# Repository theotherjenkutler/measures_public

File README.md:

# Measures
## An ecosystem for detection of physiological indicators of empathy.
<p>MEASURES is a flexible web based, AI driven eco-system which lends itself to live performance, 
<br>installation in a gallery museum, festival or alone in one's bedroom while being simple enough 
<br>for anyone with WIFI and a smartphone to use.
<br>It fuses technology and emotion where technology is often sterile and intellectual and offers 
<br>tools for self reflection while creating a method of studying the phenomenon of empathy as a whole. 
<br>Ultimately, MEASURES offers a new way to feel connected and to experience one another across borders, 
<br>cultures, socioeconomic classes and other zones of isolation.

<p>Users wear an electronic wristband which provides audio cues and measures the participant's electrodermal
<br>activity. The data is transferred over WIFI to a server which processes the data and generates a unique sound work.
<br>Each sound work produced by a participant is subsequently analyzed for point of “excitation” using Opensmile 
<br>feature extraction trained by a custom piece specific data set. The results are used as the basis of the following 
<br>user's auditory stimuli and physiological data comparison to generate the next sound piece and so on. The sound 
<br>works are added to a public online archive. Participants can choose to disclose their identity or remain anonymous.
<br>To my knowledge, MEASURES is the first system in the artistic and scientific communities designed with the 
<br>specific purpose of quantifying and measuring empathy from auditory cues. MEASURES content originates from an 
<br>infinitely expansive pool of participant data is comprised of empathetic responses for an AI driven art work.

<p>The goals of this piece put the wealth seeking uses of AI such as advertising, facial/voice recognition, fraud 
<br>prevention and other commercial applications in the background. It focuses on AI as a tool to witness people in 
<br>the most human way possible – through experiencing a person feeling empathy.
<br>The form of MEASURES is also unique because the data collection device exists as an electronic art object and 
<br>generates an expansive bio-data driven archive of individual sound works, and is designed to be extremely 
<br>accessible as a tool for installation, real-time performance and solitary use.

<p>The hardware uses a custom EDA sensor based on the AD8608 op-amp and handmade carbon silicone sensor pads.
<br>MP3 decoding is handled by the VS1053b chip connected to the ESP32WROVER over SPI.
<br>For ADC it uses an ADS1115 IC over the I2C Bus. 
 
<p>This repo will include 
<br>- Arduino firmware code for the ESP32-WROVER,
<br>- Node-Red code with respective shell scripts, 
<br>- PureData patches for sonification, 
<br>- EAGLE CAD files of schematics and PCB layout,
<br>- TensorFlow and Pytorch code

<p>Server Requirements:
<br>- Ubuntu or similar
<br>- Icecast2 // icecast.org
<br>- FFMPEG // ffmpeg.org
<br>- PureData // puredata.info
<br>- Node-Red // nodered.org
<br>- inotifytools // https://github.com/inotify-tools/inotify-tools

<p>Device Firmware Requirements:
<br>- Arduino IDE + ESP32 Arduino
<br>- External Libraries:
<br>- Adafruit_VS1053 // https://github.com/adafruit/Adafruit_VS1053_Library
<br>- WiFi Manager // https://github.com/tzapu/WiFiManager
<br>- ADS1X15 // https://github.com/RobTillaart/ADS1X15

<p>Detailed system description:
<br>TODO

<p>Relavent links/Bibliography:
<br>TODO
<br>https://arxiv.org/pdf/2008.09743.pdf Guanghao Yin, Shouqian Sun, Dian Yu and Kejun Zhang*, Member, 
<br>IEEE in their paper A Efficient Multimodal Framework for Large Scale Emotion Recognition by Fusing Music 
<br>and Electrodermal Activity Signals. openSMILE https://audeering.github.io/opensmile/ to obtain external feature 
<br>vectors of audio cues

 <br>Measures is made possible in part by the New York State Council on the Arts with the support of the Office of 
 <br>the Governor and the New York State Legislature and Wave Farm.
<br>

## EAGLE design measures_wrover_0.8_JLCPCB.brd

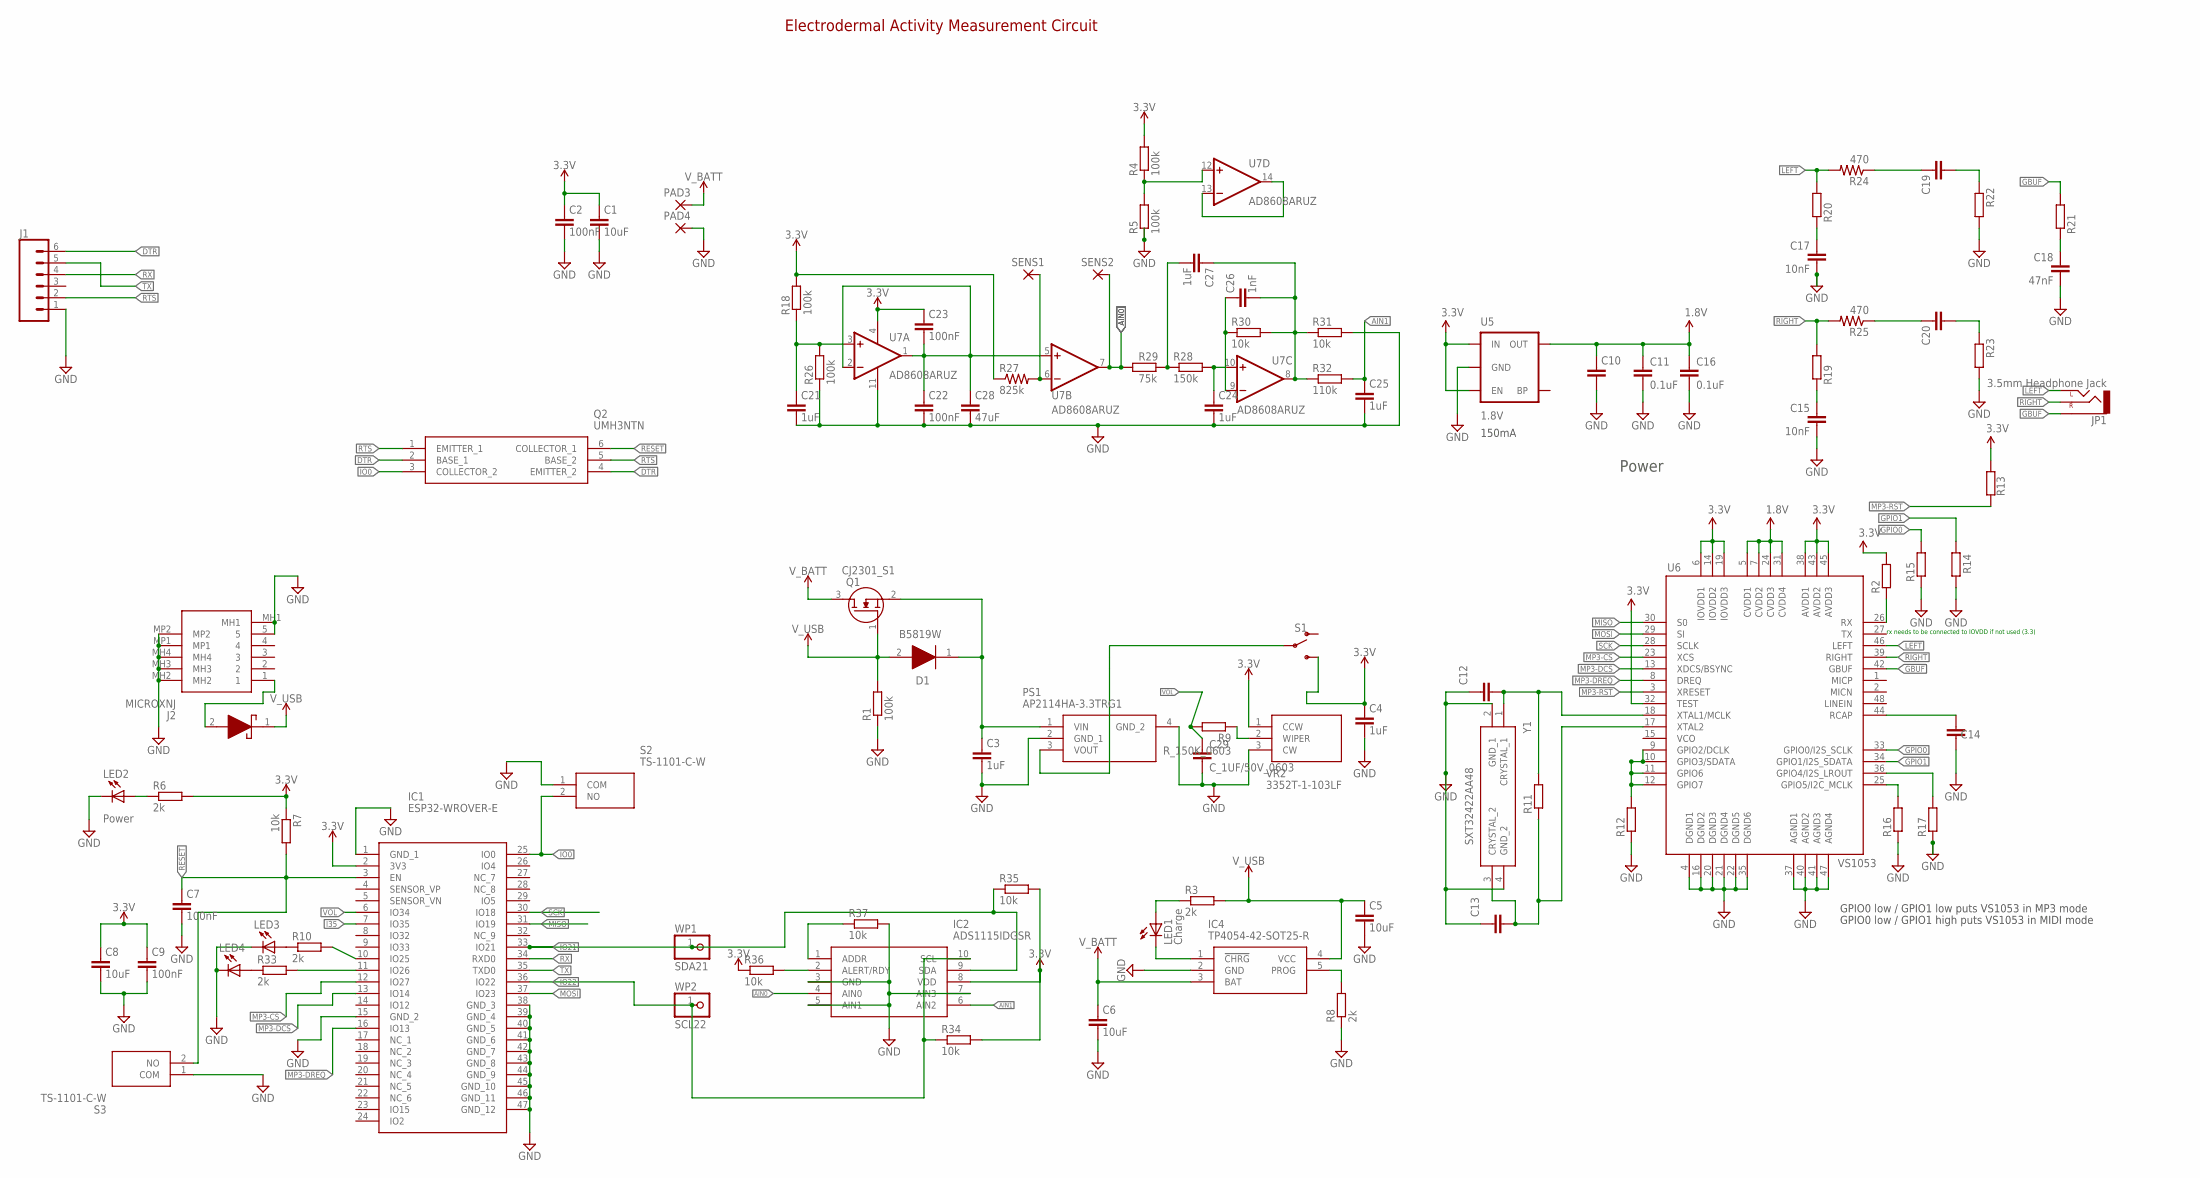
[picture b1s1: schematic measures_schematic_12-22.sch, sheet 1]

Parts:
C1, C5, C6, C8, C10, C19, C20: 10uF; C0603
C2, C7, C9, C22, C23: 100nF; C0603
C3, C4, C21, C25: 1uF; C0402
C11, C16: 0.1uF; 0603-CAP
C12, C13: 22pF; C0603
C14: 1.0uF; C0402
C15, C17: 10nF; 0603-CAP
C18: 47nF; 0603-CAP
C24, C27: 1uF; C0603
C26: 1nF; C0603
C28: 47uF; C1206
C29: C_1UF/50V_0603; C0603
D1: B5819W; SOD3716X125N
D5: BAT760-7; SOD2513X120N
IC1: ESP32-WROVER-E; ESP32WROVERE
IC2: ADS1115IDGSR; SOP50P490X110-10N
IC4: TP4054-42-SOT25-R; SOT95P280X100-5N
J1: CONN_06NO_SILK_FEMALE_PTH; 1X06_NO_SILK
J2: MICROXNJ
JP1: 3.5mm Headphone Jack; AUDIO-JACK-3.5MM-SMD
LED1: Charge; CHIP-LED0603
LED2, LED3, LED4: Power; CHIP-LED0603
PAD3, PAD4: 2,54/0,8
PS1: AP2114HA-3.3TRG1; SOT230P700X180-4N
Q1: CJ2301_S1; SOT95P240X115-3N
Q2: UMH3NTN
R1, R2, R4, R5, R12, R13, R14, R15, R16, R17, R18, R26: 100k; R0603
R3, R6, R8, R10, R33: 2k; R0603
R7, R30, R31, R34, R35, R36, R37: 10k; R0603
R9: R_150K_0603; R0603
R11: 1M; R0603
R19, R20: 20; R0603
R21: 10; R0603
R22, R23: 10K; R0603
R24, R25: 470; 0603-RES
R27: 825k; R0402
R28: 150k; R0402
R29: 75k; R0402
R32: 110k; R0603
S1: SWITCH-SPDT-PTH-11.6X4.0MM; SWITCH_SPDT_PTH_11.6X4.0MM
S2, S3: TS-1101-C-W; TS1101CW
SENS1, SENS2: 2,54/0,8
U5: 1.8V; SC70
U6: VS1053; LQFP-48
U7: AD8608ARUZ; TSSOP14
VR2: 3352T-1-103LF; 3352T1103LF
WP1: SDA21; WPAD-1-0805
WP2: SCL22; WPAD-1-0805
Y1: SXT32422AA48

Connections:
1.8V: C10.1, C11.1, C16.1, U5.5 (OUT), U6.5 (CVDD1), U6.7 (CVDD2), U6.24 (CVDD3), U6.31 (CVDD4)
AIN0: IC2.4 (AIN0), R29.1, SENS2.1, U7.7 (OUT)
AIN1: C25.1, IC2.6 (AIN2), R32.2
DTR: J1.6, Q2.2 (BASE_1), Q2.4 (EMITTER_2)
G1: R12.2, U6.9 (GPIO2/DCLK), U6.10 (GPIO3/SDATA), U6.11 (GPIO6), U6.12 (GPIO7)
G2: R16.2, U6.25 (GPIO5/I2C_MCLK)
GBUF: JP1.SLEEVE, R21.2, U6.42 (GBUF)
GND: C1.2, C2.2, C3.2, C4.2, C5.2, C6.2, C7.2, C8.2, C9.2, C10.2, C11.2, C12.1, C13.1, C14.1, C15.2, C16.2, C17.2, C18.2, C21.2, C22.2, C24.2, C25.2, C28.2, C29.2, IC1.1 (GND_1), IC1.15 (GND_2), IC1.38 (GND_3), IC1.39 (GND_4), IC1.40 (GND_5), IC1.41 (GND_6), IC1.42 (GND_7), IC1.43 (GND_8), IC1.44 (GND_9), IC1.45 (GND_10), IC1.46 (GND_11), IC1.47 (GND_12), IC2.3 (GND), IC2.5 (AIN1), IC2.7 (AIN3), IC4.2 (GND), J1.1, J2.5, J2.MH1, J2.MH2, J2.MH3, J2.MH4, J2.MP1, J2.MP2, LED2.C, LED3.C, LED4.C, PAD4.1, PS1.2 (GND_1), PS1.4 (GND_2), R1.1, R5.1, R8.1, R12.1, R14.1, R15.1, R16.1, R17.1, R22.2, R23.2, R26.1, R31.2, R37.2, S2.1 (COM), S3.1 (COM), U5.2 (GND), U6.4 (DGND1), U6.16 (DGND2), U6.20 (DGND3), U6.21 (DGND4), U6.22 (DGND5), U6.35 (DGND6), U6.37 (AGND1), U6.40 (AGND2), U6.41 (AGND3), U6.47 (AGND4), U7.11 (GND), VR2.3 (CW), Y1.2 (GND_1), Y1.4 (GND_2)
GPIO0: R15.2, U6.33 (GPIO0/I2S_SCLK)
GPIO1: R14.2, U6.34 (GPIO1/I2S_SDATA)
GPIO4: R17.2, U6.36 (GPIO4/I2S_LROUT)
I35: IC1.7 (IO35)
IO0: IC1.25 (IO0), Q2.3 (COLLECTOR_2), S2.2 (NO)
IO21: IC1.33 (IO21), IC2.9 (SDA), R35.1, WP1.1
IO22: IC1.36 (IO22), IC2.10 (SCL), R34.1, WP2.1
LEFT: JP1.TIP (LEFT), R20.2, R24.2, U6.46 (LEFT)
MIDI-RX: R2.1, U6.26 (RX)
MISO: IC1.31 (IO19), U6.30 (S0)
MOSI: IC1.37 (IO23), U6.29 (SI)
MP3-CS: IC1.12 (IO27), U6.23 (XCS)
MP3-DCS: IC1.13 (IO14), U6.13 (XDCS/BSYNC)
MP3-DREQ: IC1.16 (IO13), U6.8 (DREQ)
unnamed: PS1.3 (VOUT), S1.2
unnamed: C3.1, D1.1 (K), PS1.1 (VIN), Q1.2 (S)
unnamed: LED2.A, R6.1
unnamed: IC4.1 (!CHRG), LED1.C
unnamed: LED1.A, R3.1
unnamed: D5.2 (A), J2.1
unnamed: IC4.5 (PROG), R8.2
unnamed: R9.1, VR2.2 (WIPER)
unnamed: R4.1, R5.2, U7.12 (+IN)
unnamed: U7.13 (-IN), U7.14 (OUT)
unnamed: IC1.10 (IO25), R10.2
unnamed: IC1.11 (IO26), R33.2
unnamed: C12.2, R11.2, U6.18 (XTAL1/MCLK), Y1.1 (CRYSTAL_1)
unnamed: C13.2, R11.1, U6.17 (XTAL2), Y1.3 (CRYSTAL_2)
unnamed: C18.1, R21.1
unnamed: C17.1, R20.1
unnamed: C15.1, R19.1
unnamed: C20.1, R25.1
unnamed: C19.1, R24.1
unnamed: C21.1, R18.1, R26.2, U7.3 (+IN)
unnamed: C22.1, C23.2, C28.1, U7.1 (OUT), U7.2 (-IN), U7.5 (+IN)
unnamed: R27.2, SENS1.1, U7.6 (-IN)
unnamed: C24.1, R28.2, U7.10 (+IN)
unnamed: C26.2, C27.1, R30.2, R31.1, R32.1, U7.8 (OUT)
unnamed: C26.1, R30.1, U7.9 (-IN)
unnamed: C27.2, R28.1, R29.2
unnamed: LED3.A, R10.1
unnamed: LED4.A, R33.1
unnamed: IC2.2 (ALERT/RDY), R36.2
unnamed: IC2.1 (ADDR), R37.1
RCAP: C14.2, U6.44 (RCAP)
RESET: C7.1, IC1.3 (EN), Q2.6 (COLLECTOR_1), R7.2, S3.2 (NO)
RIGHT: JP1.RING (RIGHT), R19.2, R25.2, U6.39 (RIGHT)
RTS: J1.2, Q2.1 (EMITTER_1), Q2.5 (BASE_2)
RX: IC1.34 (RXD0), J1.4
SCK: IC1.30 (IO18), U6.28 (SCLK)
SPKR-L: C19.2, R22.1
SPKR-R: C20.2, R23.1
TX: IC1.35 (TXD0), J1.5
VOL: C29.1, IC1.6 (IO34), R9.2
V_BATT: C6.1, IC4.3 (BAT), PAD3.1, Q1.3 (D)
V_USB: C5.1, D1.2 (A), D5.1 (K), IC4.4 (VCC), Q1.1 (G), R1.2, R3.2

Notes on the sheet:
Power
150mA
GPIO0 low / GPIO1 high puts VS1053 in MIDI mode
GPIO0 low / GPIO1 low puts VS1053 in MP3 mode
Electrodermal Activity Measurement Circuit
rx needs to be connected to IOVDD if not used (3.3)

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
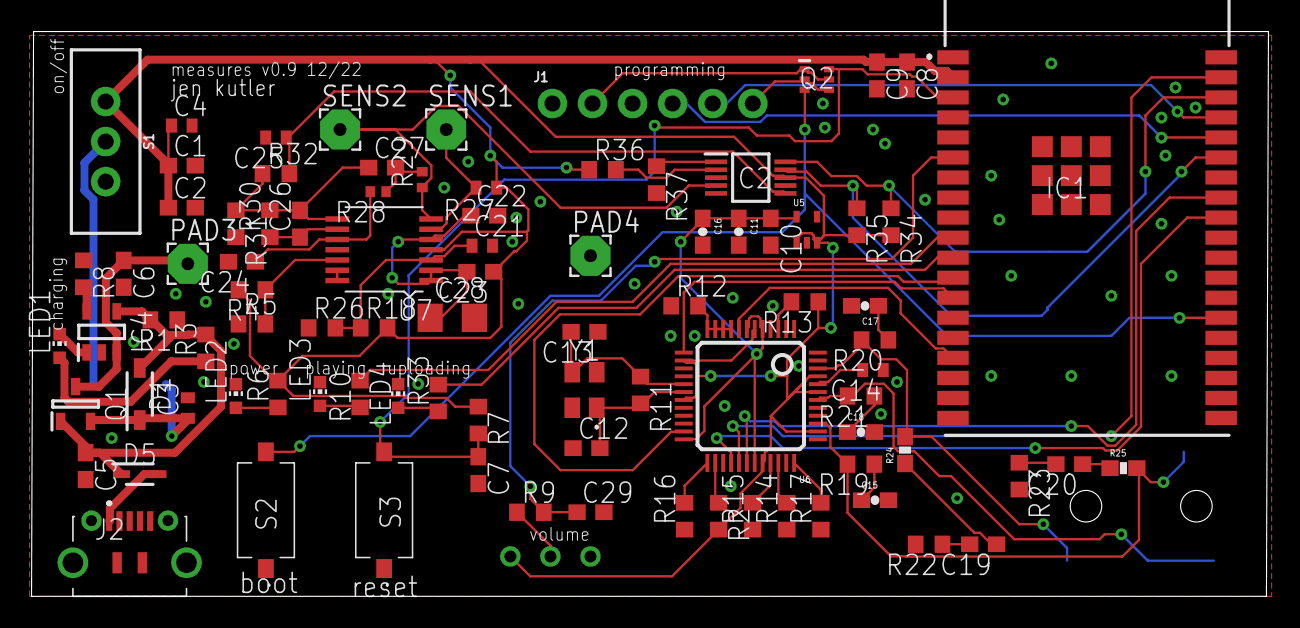
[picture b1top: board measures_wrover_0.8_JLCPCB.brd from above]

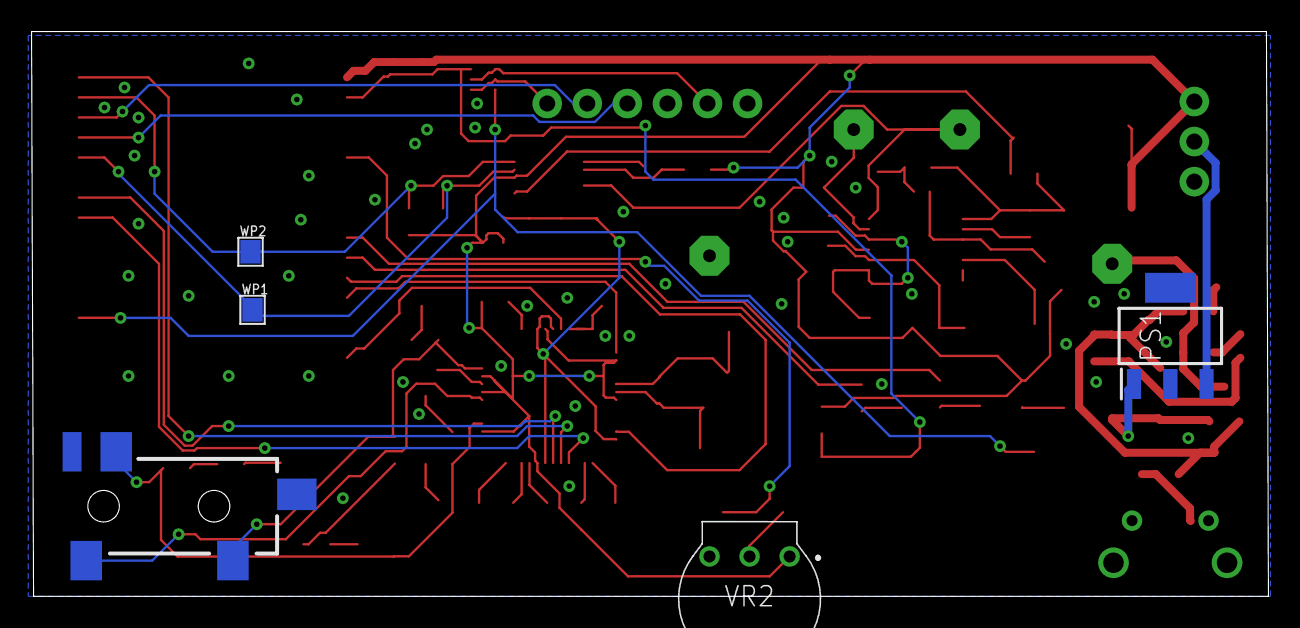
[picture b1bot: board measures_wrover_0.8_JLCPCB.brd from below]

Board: 2 copper layers, 78.4 x 35.8 mm, 95 parts (5 on the bottom side), 65 nets.

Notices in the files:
parts and their libraries:
SparkFun-PowerSymbols: Licensing: Creative Commons ShareAlike 4.0 International - https://creativecommons.org/licenses/by-sa/4.0
SparkFun-DigitalIC: Licensing: CC v3.0 Share-Alike You are welcome to use this library for commercial purposes.
